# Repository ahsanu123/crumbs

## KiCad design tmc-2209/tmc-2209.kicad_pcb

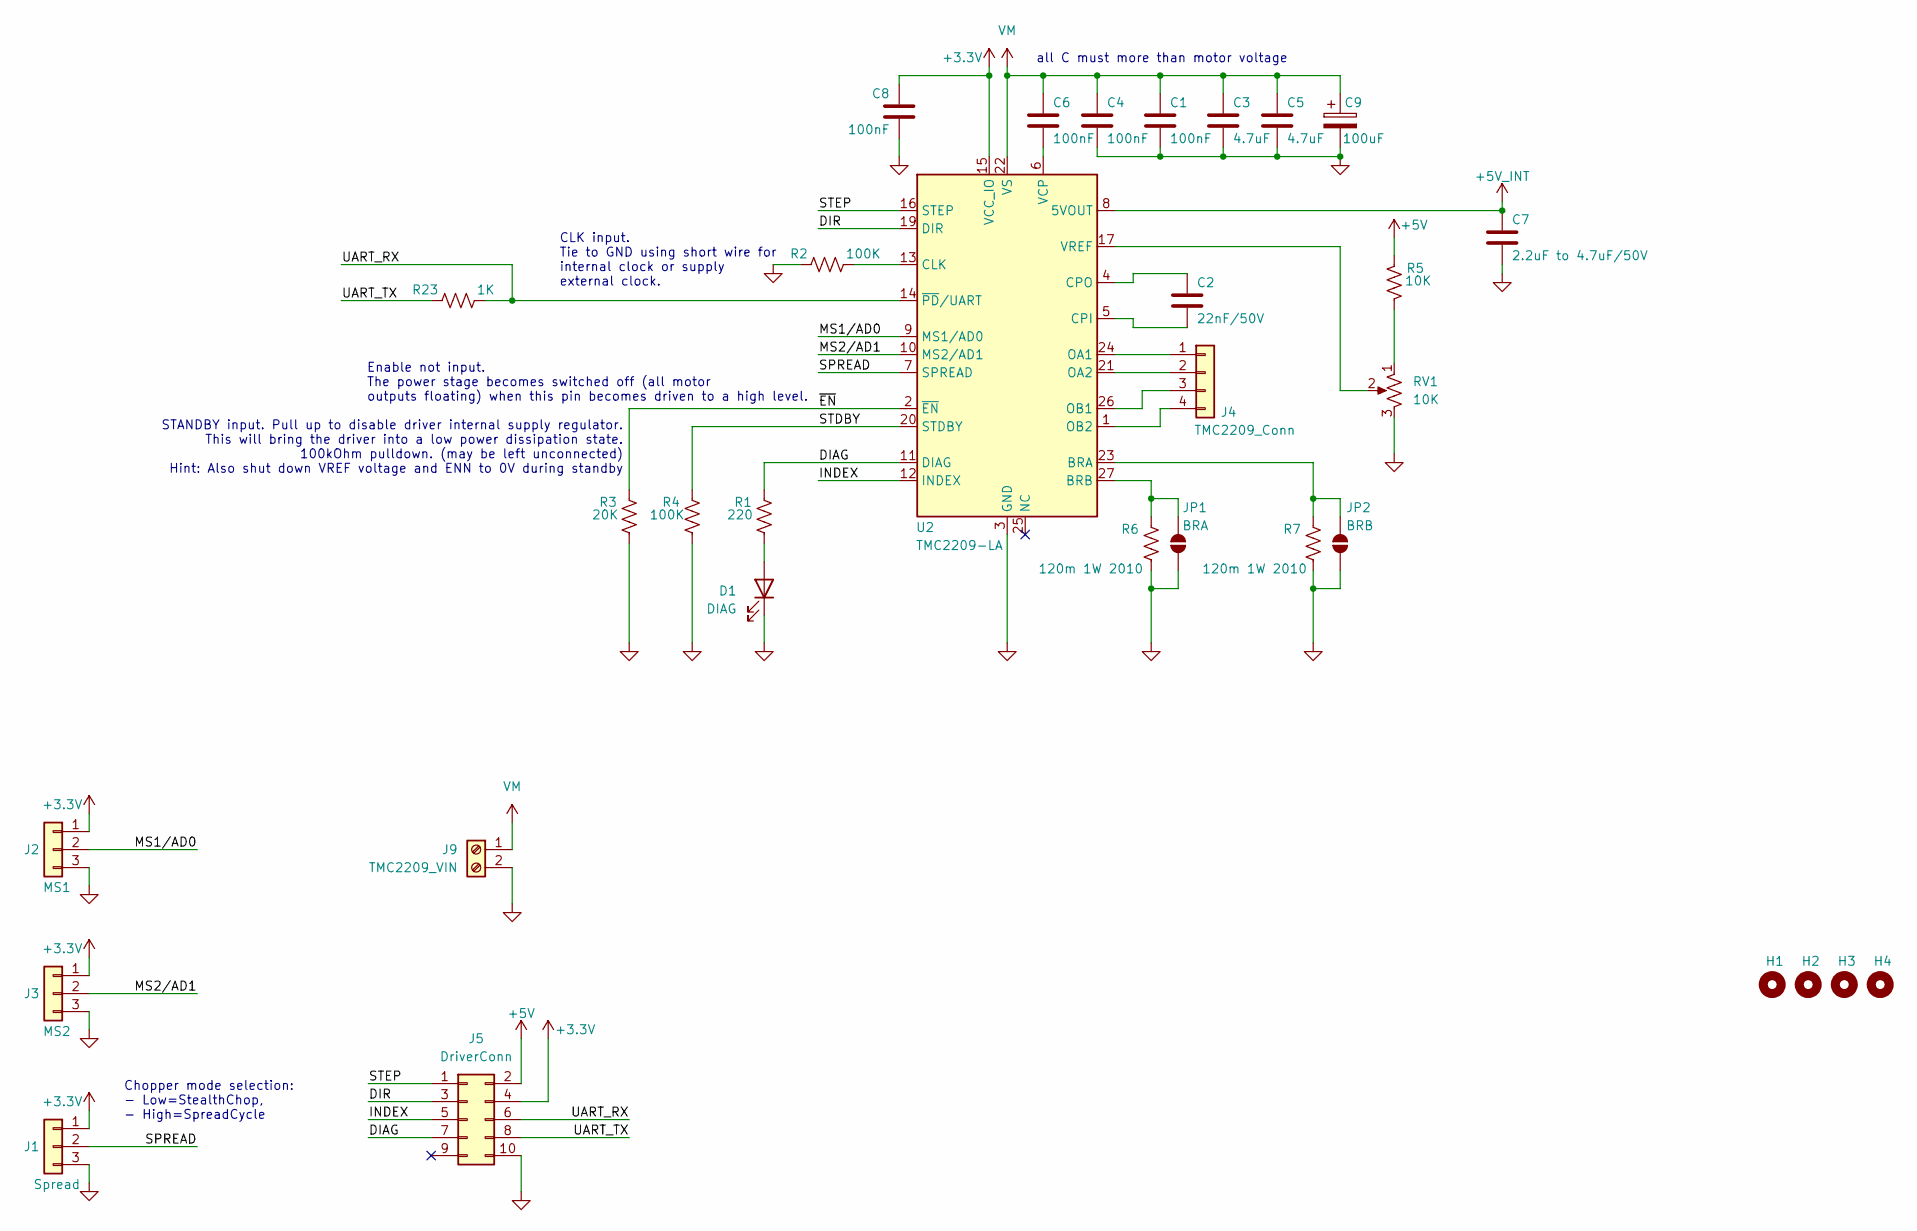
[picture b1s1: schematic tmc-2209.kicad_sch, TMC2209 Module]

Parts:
C1, C4, C6, C8: 100nF; C_0805_2012Metric_Pad1.18x1.45mm_HandSolder
C2: 22nF/50V; C_0805_2012Metric_Pad1.18x1.45mm_HandSolder
C3, C5: 4.7uF; C_0805_2012Metric_Pad1.18x1.45mm_HandSolder
C7: 2.2uF to 4.7uF/50V; C_0805_2012Metric_Pad1.18x1.45mm_HandSolder
C9: 100uF; CP_Radial_D8.0mm_P3.50mm
D1: DIAG; LED_0805_2012Metric_Pad1.15x1.40mm_HandSolder
H1, H2, H3, H4: MountingHole; MountingHole_2mm
J1: Spread; PinHeader_1x03_P2.54mm_Vertical
J2: MS1; PinHeader_1x03_P2.54mm_Vertical
J3: MS2; PinHeader_1x03_P2.54mm_Vertical
J4: TMC2209_Conn; Molex_Nano-Fit_105313-xx04_1x04_P2.50mm_Horizontal
J5: DriverConn; IDC-Header_2x05_P2.54mm_Vertical
J9: TMC2209_VIN; TerminalBlock_Phoenix_PT-1,5-2-5.0-H_1x02_P5.00mm_Horizontal
JP1: BRA; SolderJumper-2_P1.3mm_Open_RoundedPad1.0x1.5mm
JP2: BRB; SolderJumper-2_P1.3mm_Open_RoundedPad1.0x1.5mm
R1: 220; R_0805_2012Metric_Pad1.20x1.40mm_HandSolder
R2, R4: 100K; R_0805_2012Metric_Pad1.20x1.40mm_HandSolder
R3: 20K; R_0805_2012Metric_Pad1.20x1.40mm_HandSolder
R5: 10K; R_0805_2012Metric_Pad1.20x1.40mm_HandSolder
R6, R7: 120m 1W 2010; R_2010_5025Metric
R23: 1K; R_0805_2012Metric_Pad1.20x1.40mm_HandSolder
RV1: 10K; Potentiometer_Bourns_3269W_Vertical
U2: TMC2209-LA; VQFN-28-1EP_5x5mm_P0.5mm_EP3.7x3.7mm

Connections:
+3.3V: C8.1, J1.1, J2.1, J3.1, J5.4, U2.15 (VCC_IO)
+5V: J5.2, R5.1
+5V_INT: C7.1, U2.8 (5VOUT)
/DIAG: J5.7, R1.1, U2.11 (DIAG)
/DIR: J5.3, U2.19 (DIR)
/INDEX: J5.5, U2.12 (INDEX)
/MS1/AD0: J2.2, U2.9 (MS1/AD0)
/MS2/AD1: J3.2, U2.10 (MS2/AD1)
/SPREAD: J1.2, U2.7 (SPREAD)
/STDBY: R4.1, U2.20 (STDBY)
/STEP: J5.1, U2.16 (STEP)
/UART_RX: J5.6, R23.1, U2.14 (~PD/UART)
/UART_TX: J5.8, R23.2
/~EN: R3.1, U2.2 (~EN)
GND: C1.2, C3.2, C4.2, C5.2, C7.2, C8.2, C9.2, D1.1 (K), J1.3, J2.3, J3.3, J5.10, J9.2, JP1.1 (A), JP2.1 (A), R2.2, R3.2, R4.2, R6.2, R7.2, RV1.3, U2.3 (GND), U2.18 (GND), U2.29 (GND)
unnamed: D1.2 (A), R1.2
unnamed: J4.1, U2.24 (OA1)
unnamed: J4.2, U2.21 (OA2)
unnamed: J4.3, U2.26 (OB1)
unnamed: J4.4, U2.1 (OB2)
unnamed: JP1.2 (B), R6.1, U2.27 (BRB)
unnamed: JP2.2 (B), R7.1, U2.23 (BRA)
unnamed: R5.2, RV1.1
unnamed: R2.1, U2.13 (CLK)
unnamed: C2.2, U2.5 (CPI)
unnamed: C2.1, U2.4 (CPO)
unnamed: C6.2, U2.6 (VCP)
unnamed: RV1.2, U2.17 (VREF)
VM: C1.1, C3.1, C4.1, C5.1, C6.1, C9.1, J9.1, U2.22 (VS), U2.28 (VS)

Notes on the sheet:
Chopper mode selection: - Low=StealthChop, - High=SpreadCycle
all C must more than motor voltage
Enable not input. The power stage becomes switched off (all motor outputs floating) when this pin becomes driven to a high level.
STANDBY input. Pull up to disable driver internal supply regulator. This will bring the driver into a low power dissipation state. 100kOhm pulldown. (may be left unconnected) Hint: Also shut down VREF voltage and ENN to 0V during standby
CLK input. Tie to GND using short wire for internal clock or supply external clock.

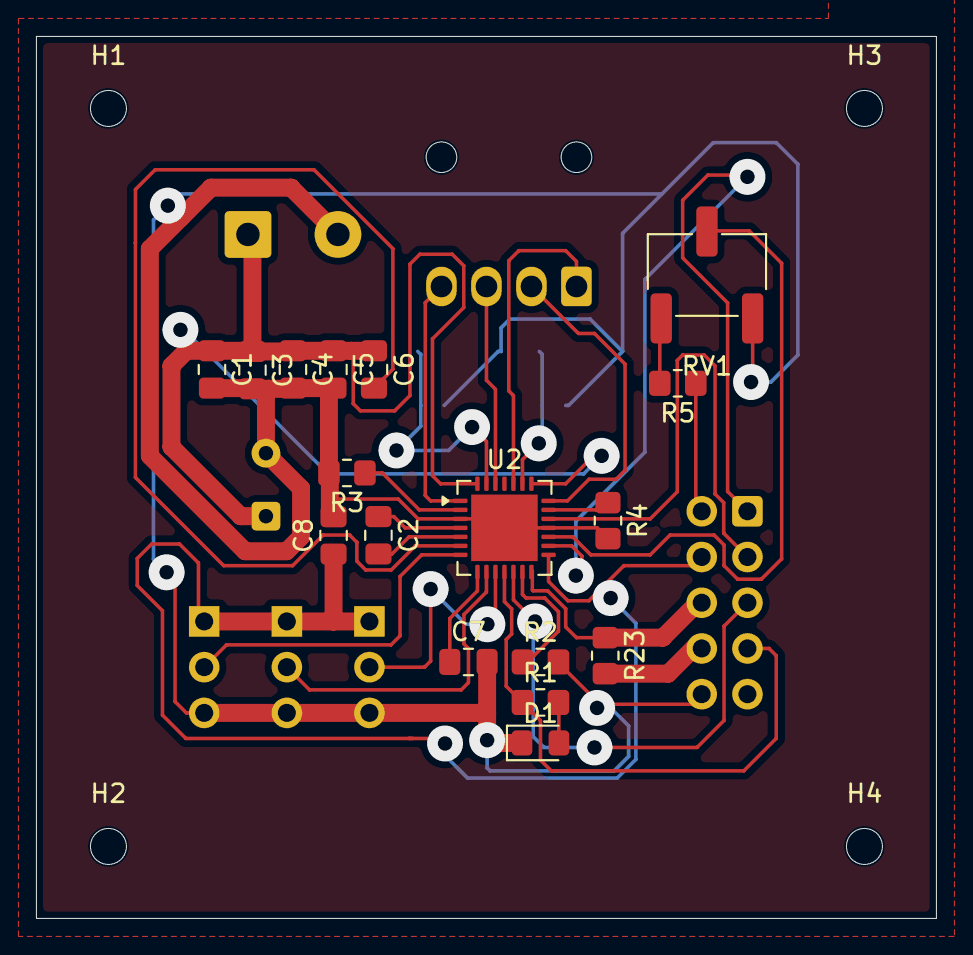
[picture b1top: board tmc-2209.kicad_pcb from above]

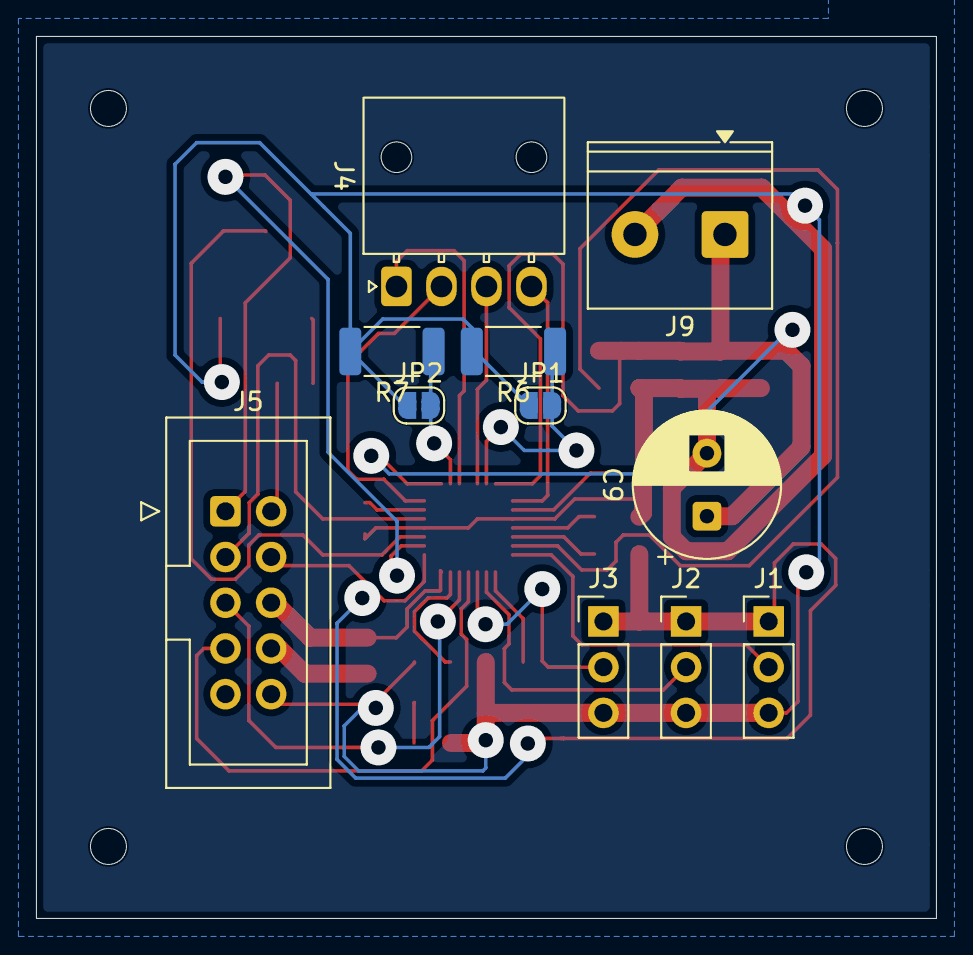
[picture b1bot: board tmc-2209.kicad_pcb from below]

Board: 2 copper layers, 50.0 x 49.0 mm, 32 parts (11 on the bottom side), 29 nets.
